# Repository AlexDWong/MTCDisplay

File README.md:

# MTCDisplay

## Description
MTCDisplay is an Arduino-based MIDI Timecode visual display that allows users to view a MIDI Timecode stream on an external LED display. The goal of this project was to create a simple display to enable lighting, audio, and video equipment operators to visually monitor a timecode stream without spending $400+ on a fully-integrated solution.

## Updates
**9/28/2016:** Board version 1.1; see directory for changes.

**8/8/2016:** Board version 1.0 proven.

## Features
* MIDI IN/THRU (DIN-5 connector)
  * 1x MIDI IN
  * Up to 3x MIDI THRU
* 12VDC input with polarity and over-current protection
* Supports all MTC framerates (24, 25, 29.97, 30)
* Mounting holes for custom enclosures and edge clearance for extruded aluminum enclosures

## Physical
* Board Dimensions: 5.00" x 3.35" (127mm x 85.09mm)
* Board Thickness: 1.6mm
* Input Power: +12VDC, 1A (max)
* Input Connections: 2.1mm DC barrel jack, MIDI (DIN-5)
* Output Connections: Up to 3x MIDI (DIN-5)
* Mounting: 4x 0.125" holes at edges of board, 0.1" clearance on sides for insertion into extruded aluminum case

## How it works
MTCDisplay accepts input from a MIDI Timecode stream and displays it on a large, 7-segment display. The displays are driven and controlled by a MAX7219 driver, enabling the Arduino to focus on decoding the MIDI Timecode stream. MTCDisplay supports all four MTC framerates (24/25/29.97 drop-frame/30 frames/s), and the design can be scaled up to support almost any 7-segment, common-cathode LED display.

### "What's (MIDI) Timecode?"

Timecode is a way to synchronize equipment with each other; for instance, an audio track could output a timecode stream to a lighting console so that lighting cues are triggered at exactly the right moment. [MIDI Timecode (MTC)](https://en.wikipedia.org/wiki/MIDI_timecode) is timecode transmitted between devices using the MIDI protocol and interface, and is based off [SMPTE Timecode](https://en.wikipedia.org/wiki/SMPTE_timecode). 

You can read more about the MIDI protocol on [Wikipedia](https://en.wikipedia.org/wiki/MIDI) or on the [official MIDI Association website](https://www.midi.org/). 

### MIDI Timecode

MIDI Timecode follows the SMPTE standard for timecode. Each timecode is represented as four 8-bit unsigned integers:
* Hours (hh)
* Minutes (mm)
* Seconds (ss)
* Frames (ff)

Hours, minutes and seconds are self-explanatory. Frames are sub-divisions of seconds, originally referring to a frame of film as SMPTE timecode was originally developed for film use. There are several different framerates, and as a result MIDI Timecode must also transmit the framerate to ensure all devices are kept in sync.

MIDI Timecode messages can take one of two forms:

#### Quarter-frame Timecode

Quarter-frame Timecode messages are used when the timecode stream is running. Each hour, minute, second or frame byte is broken down into two 4-bit values and attached to a 3-bit identifier. Before each piece is sent, it is preceded by a single status byte (0xF1).

| Piece |  ID #  |  Data  |  Full Byte  | Description         |
|:-----:|:------:|:------:|:-----------:|---------------------|
| 0     | `0000` | `ffff` | `0000 ffff` | Frame number lsbits |
| 1     | `0001` | `000f` | `0001 000f` | Frame number msbit  |
| 2     | `0010` | `ssss` | `0010 ssss` | Seconds lsbits      |
| 3     | `0011` | `00ss` | `0011 00ss` | Seconds msbits      |
| 4     | `0100` | `mmmm` | `0100 mmmm` | Minutes lsbits      |
| 5     | `0101` | `00mm` | `0101 00mm` | Minutes msbits      |
| 6     | `0110` | `hhhh` | `0110 hhhh` | Hour lsbits         |
| 7     | `0111` | `0rrh` | `0111 0rrh` | Hour msbit and rate |

**EX:** Timecode = 01:02:03:04, framerate = 30 frames/s

Quarter-frame Timecode = `F1 04 F1 10 F1 23 F1 30 F1 42 F1 50 F1 61 F1 76`

*Source: [Wikipedia](https://en.wikipedia.org/wiki/MIDI_timecode)*

#### Full Timecode

If the timecode stream suddenly jumps (i.e. jumping ahead in an audio track) a full timecode is sent so that all equipment can resync. Full timecode messages are 10 bytes long, and once transmitted the MTC stream reverts back to quarter-frame messages; full timecode messages are structured as follows:
	`F0 7F 7F 01 01 hh mm ss ff F7`
In it's current state, MTCDisplay only supports quarter-frame messages. If the timecode input jumps, the change will not be reflected on MTCDisplay until the next quarter-frame message is received.

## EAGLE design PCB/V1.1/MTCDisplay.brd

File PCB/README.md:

#PCB Files

Enclosed here are the files needed to have a PCB manufactured, as well as a Bill of Materials.

## Important Note:
The LED displays do not need a current-limiting resistor; instead, the current is set by an external pullup resistor on the MAX7219. If you choose to use a different 7-segment display, then you may need to select a different value for R12 depending on the per-segment forward voltage and foward current. The [MAX7219 datasheet (PDF)](https://datasheets.maximintegrated.com/en/ds/MAX7219-MAX7221.pdf) contains a table with approximate resistance values for a range of voltages and currents; when in doubt, a higher resistance is better.

## Versions
### Version 1.1
Resolved several issues:
* All capacitors have been replaced with 0805 SMD ceramic variants to reduce board space.
* Board reduced in size slightly.
* Rearranged components for easier hand-soldering.
* LCD display package has been corrected; displays now protrude slightly over the edge of the board instead of being inset 1/4" from the edge.
* MIDI OUT/THRU switch removed; no plans to add MTC output at this time.
* Fixed silkscreen part names and text placement.
* Added 0603 LED for power indication.
* Added 0.100", 2x3 ICSP header to program Arduino directly.
* Added diode to RESET signal for ICSP support.
* Added reverse-polarity and over-current protection to input.

### Version 1.0
Initial release. This version has been tested and is proven to work as described. Only Gerber files and a BOM are included.

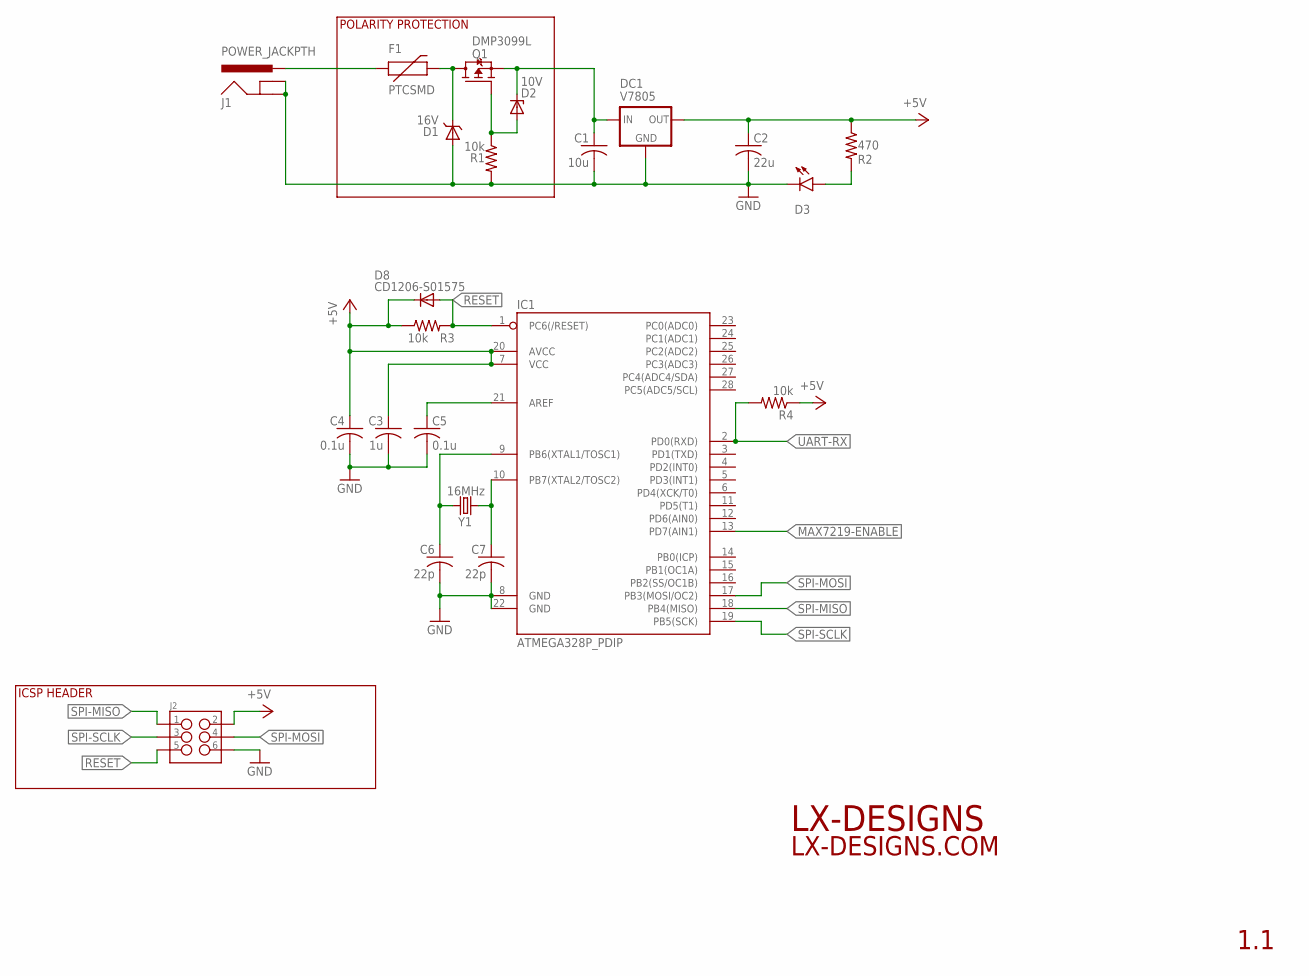
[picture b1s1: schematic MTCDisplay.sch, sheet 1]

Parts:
C1: 10u; C0805K
C2: 22u; C0805K
C3: 1u; C0805K
C4, C5: 0.1u; C0805K
C6, C7: 22p; C0805K
D1: 16V; SOD323-NOSILK
D2: 10V; SOD323
D3: LED0603; LED-0603
D8: CD1206-S01575; MINIMELF
DC1: V7805
F1: PTCSMD; PTC-1206
IC1: ATMEGA328P_PDIP; DIL28-3
J1: POWER_JACKPTH; POWER_JACK_PTH
J2: M03X2NO_SILK; 2X3-NS
Q1: DMP3099L; SOT23
R1, R3, R4: 10k; R0805
R2: 470; R0805
Y1: 16MHz; HC49US

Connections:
5V: C1.1, D2.C, DC1.IN, Q1.2 (S)
+5V: C2.1, C3.1, C4.1, D8.C, DC1.OUT, IC1.7 (VCC), IC1.20 (AVCC), J2.2, R2.1, R3.1, R4.1; also elsewhere on the board
GND: C1.2, C2.2, C3.2, C4.2, C5.2, C6.2, C7.2, D1.A, D3.C, DC1.GND, IC1.8 (GND), IC1.22 (GND), J1.GND, J1.GNDBREAK, J2.6, R1.2; also elsewhere on the board
MAX7219-ENABLE: IC1.13 (PD7(AIN1)); also elsewhere on the board
unnamed: C6.1, IC1.9 (PB6(XTAL1/TOSC1)), Y1.2
unnamed: C5.1, IC1.21 (AREF)
unnamed: D3.A, R2.2
unnamed: C7.1, IC1.10 (PB7(XTAL2/TOSC2)), Y1.1
unnamed: F1.1, J1.PWR
unnamed: D1.C, F1.2, Q1.3 (D)
unnamed: D2.A, Q1.1 (G), R1.1
RESET: D8.A, IC1.1 (PC6(/RESET)), J2.5, R3.2
SPI-MISO: IC1.18 (PB4(MISO)), J2.1
SPI-MOSI: IC1.17 (PB3(MOSI/OC2)), J2.4; also elsewhere on the board
SPI-SCLK: IC1.19 (PB5(SCK)), J2.3; also elsewhere on the board
UART-RX: IC1.2 (PD0(RXD)), R4.2; also elsewhere on the board

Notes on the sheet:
POLARITY PROTECTION
ICSP HEADER
LX-DESIGNS
LX-DESIGNS.COM
1.1

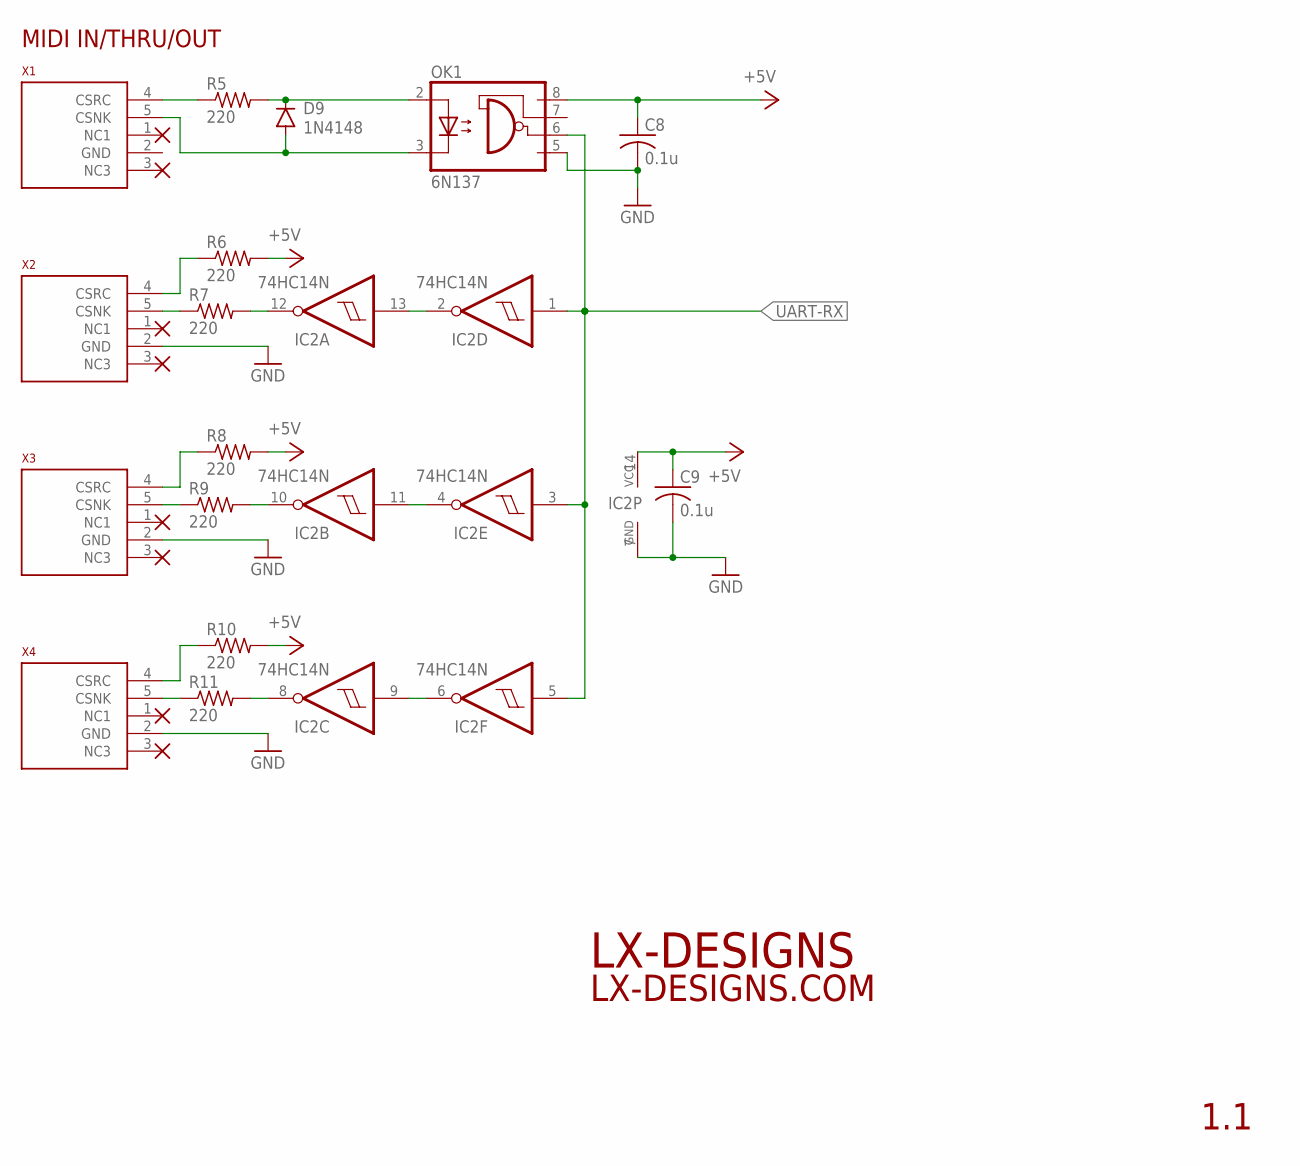
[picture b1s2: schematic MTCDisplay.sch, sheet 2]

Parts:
C8, C9: 0.1u; C0805K
D9: 1N4148; DIODE-1N4148
IC2: 74HC14N; DIL14
OK1: 6N137; DIL08
R5, R6, R7, R8, R9, R10, R11: 220; R0805
X1, X2, X3, X4: 57PC5FSWITCHCRAFT; DIN_5_FEMALE_SUPPORT

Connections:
+5V: C8.1, C9.1, IC2.14 (VCC), OK1.8 (VCC), R6.2, R8.2, R10.2; also elsewhere on the board
GND: C8.2, C9.2, IC2.7 (GND), OK1.5 (GND), X2.2 (GND), X3.2 (GND), X4.2 (GND); also elsewhere on the board
unnamed: R5.1, X1.4 (CSRC)
unnamed: D9.C, OK1.2 (A), R5.2
unnamed: D9.A, OK1.3 (C), X1.5 (CSNK)
unnamed: IC2.2 (O), IC2.13 (I)
unnamed: IC2.12 (O), R7.2
unnamed: IC2.10 (O), R9.2
unnamed: R7.1, X2.5 (CSNK)
unnamed: R6.1, X2.4 (CSRC)
unnamed: IC2.8 (O), R11.2
unnamed: R9.1, X3.5 (CSNK)
unnamed: R8.1, X3.4 (CSRC)
unnamed: IC2.4 (O), IC2.11 (I)
unnamed: IC2.6 (O), IC2.9 (I)
unnamed: R11.1, X4.5 (CSNK)
unnamed: R10.1, X4.4 (CSRC)
UART-RX: IC2.1 (I), IC2.3 (I), IC2.5 (I), OK1.6 (VO); also elsewhere on the board

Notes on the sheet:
MIDI IN/THRU/OUT
LX-DESIGNS
LX-DESIGNS.COM
1.1

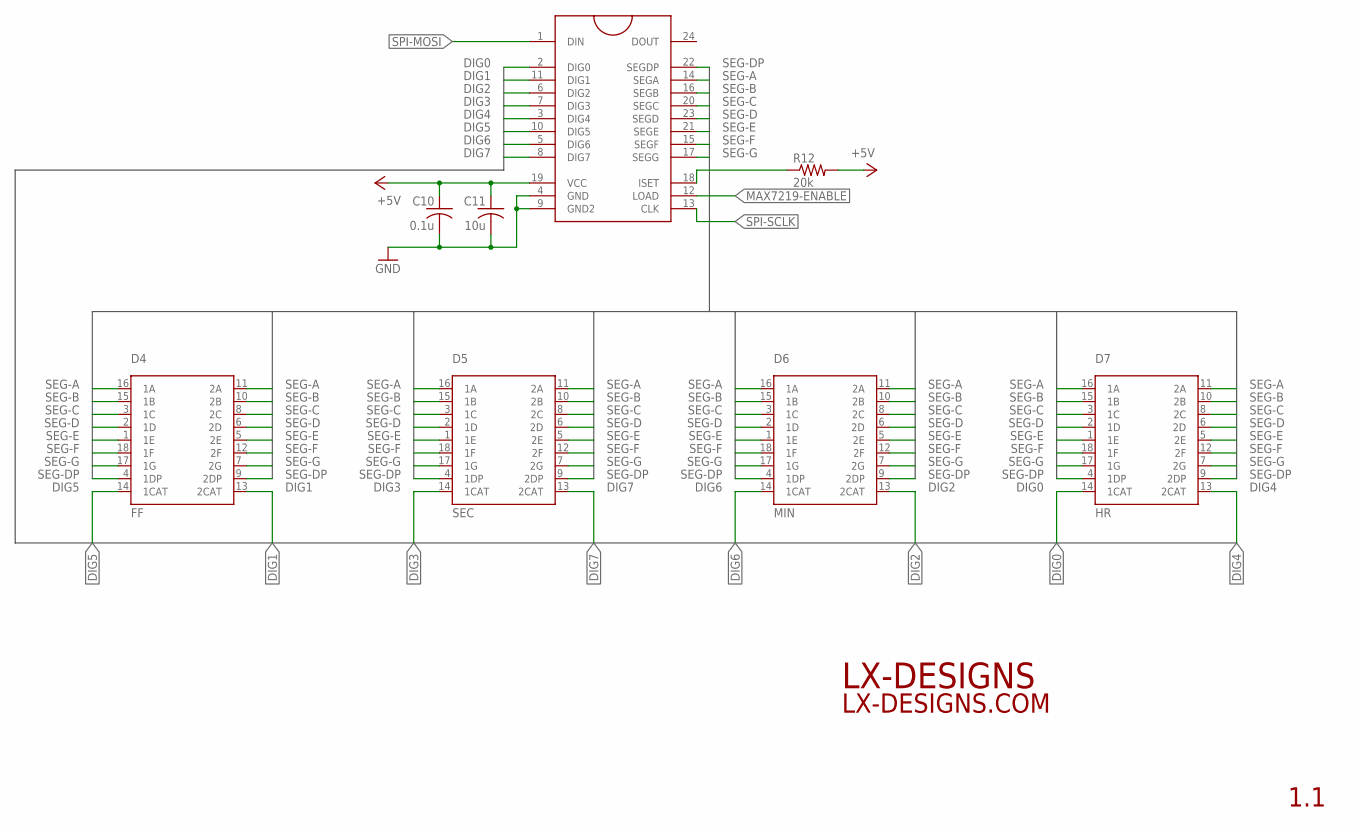
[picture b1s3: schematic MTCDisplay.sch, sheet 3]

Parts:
C10: 0.1u; C0805K
C11: 10u; C0805K
D4: FF; 299-XX-43-618-10-002000
D5: SEC; 299-XX-43-618-10-002000
D6: MIN; 299-XX-43-618-10-002000
D7: HR; 299-XX-43-618-10-002000
IC3: MAX7219DIP; DIL24
R12: 20k; R0805

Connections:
+5V: C10.1, C11.1, IC3.19 (VCC), R12.2; also elsewhere on the board
DIG0: D7.14 (1CAT), IC3.2 (DIG0)
DIG1: D4.13 (2CAT), IC3.11 (DIG1)
DIG2: D6.13 (2CAT), IC3.6 (DIG2)
DIG3: D5.14 (1CAT), IC3.7 (DIG3)
DIG4: D7.13 (2CAT), IC3.3 (DIG4)
DIG5: D4.14 (1CAT), IC3.10 (DIG5)
DIG6: D6.14 (1CAT), IC3.5 (DIG6)
DIG7: D5.13 (2CAT), IC3.8 (DIG7)
GND: C10.2, C11.2, IC3.4 (GND), IC3.9 (GND2); also elsewhere on the board
MAX7219-ENABLE: IC3.12 (LOAD); also elsewhere on the board
unnamed: IC3.18 (ISET), R12.1
SEG-A: D4.11 (2A), D4.16 (1A), D5.11 (2A), D5.16 (1A), D6.11 (2A), D6.16 (1A), D7.11 (2A), D7.16 (1A), IC3.14 (SEGA)
SEG-B: D4.10 (2B), D4.15 (1B), D5.10 (2B), D5.15 (1B), D6.10 (2B), D6.15 (1B), D7.10 (2B), D7.15 (1B), IC3.16 (SEGB)
SEG-C: D4.3 (1C), D4.8 (2C), D5.3 (1C), D5.8 (2C), D6.3 (1C), D6.8 (2C), D7.3 (1C), D7.8 (2C), IC3.20 (SEGC)
SEG-D: D4.2 (1D), D4.6 (2D), D5.2 (1D), D5.6 (2D), D6.2 (1D), D6.6 (2D), D7.2 (1D), D7.6 (2D), IC3.23 (SEGD)
SEG-DP: D4.4 (1DP), D4.9 (2DP), D5.4 (1DP), D5.9 (2DP), D6.4 (1DP), D6.9 (2DP), D7.4 (1DP), D7.9 (2DP), IC3.22 (SEGDP)
SEG-E: D4.1 (1E), D4.5 (2E), D5.1 (1E), D5.5 (2E), D6.1 (1E), D6.5 (2E), D7.1 (1E), D7.5 (2E), IC3.21 (SEGE)
SEG-F: D4.12 (2F), D4.18 (1F), D5.12 (2F), D5.18 (1F), D6.12 (2F), D6.18 (1F), D7.12 (2F), D7.18 (1F), IC3.15 (SEGF)
SEG-G: D4.7 (2G), D4.17 (1G), D5.7 (2G), D5.17 (1G), D6.7 (2G), D6.17 (1G), D7.7 (2G), D7.17 (1G), IC3.17 (SEGG)
SPI-MOSI: IC3.1 (DIN); also elsewhere on the board
SPI-SCLK: IC3.13 (CLK); also elsewhere on the board

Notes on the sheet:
LX-DESIGNS
LX-DESIGNS.COM
1.1

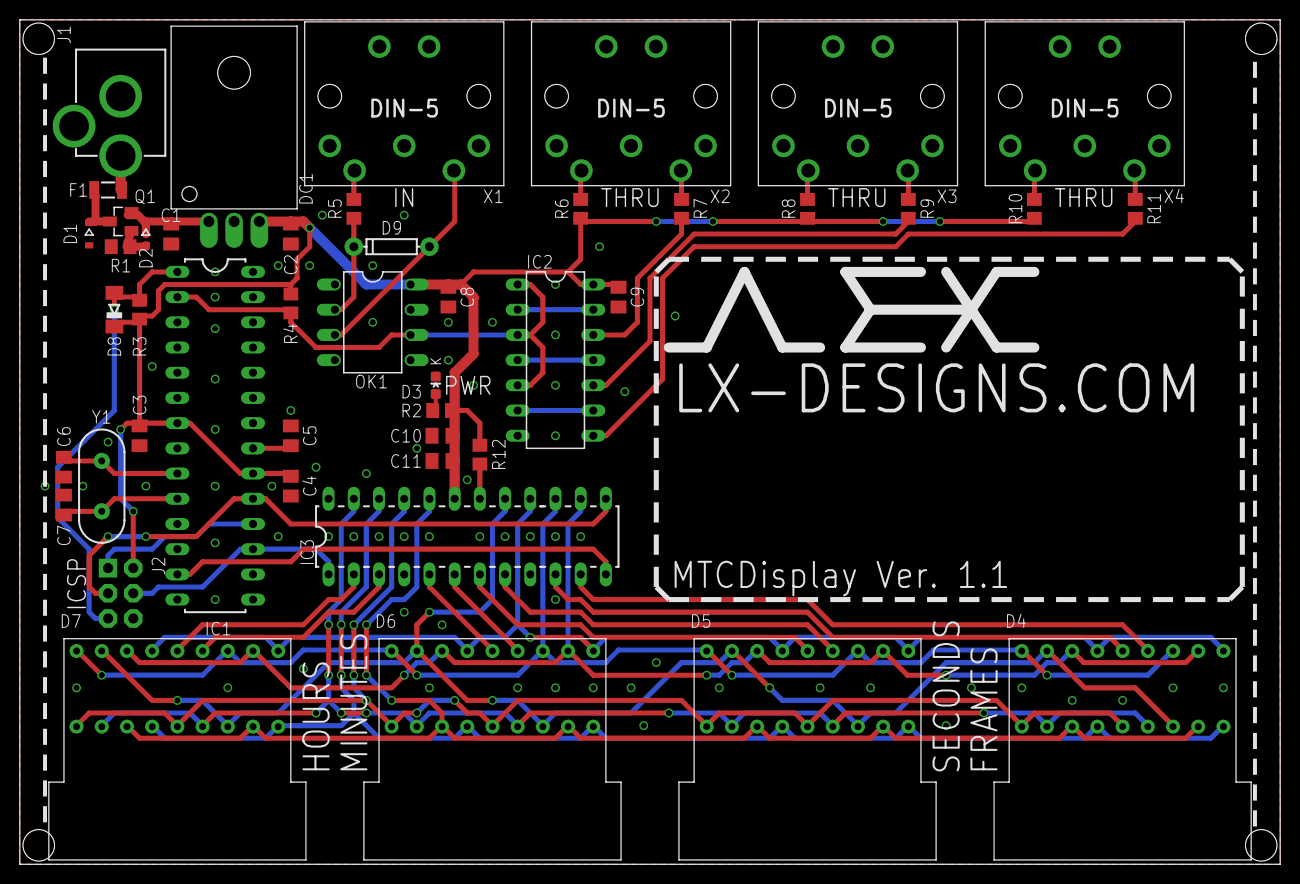
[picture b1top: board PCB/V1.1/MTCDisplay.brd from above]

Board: 2 copper layers, 127.0 x 85.1 mm, 46 parts (0 on the bottom side), 48 nets.

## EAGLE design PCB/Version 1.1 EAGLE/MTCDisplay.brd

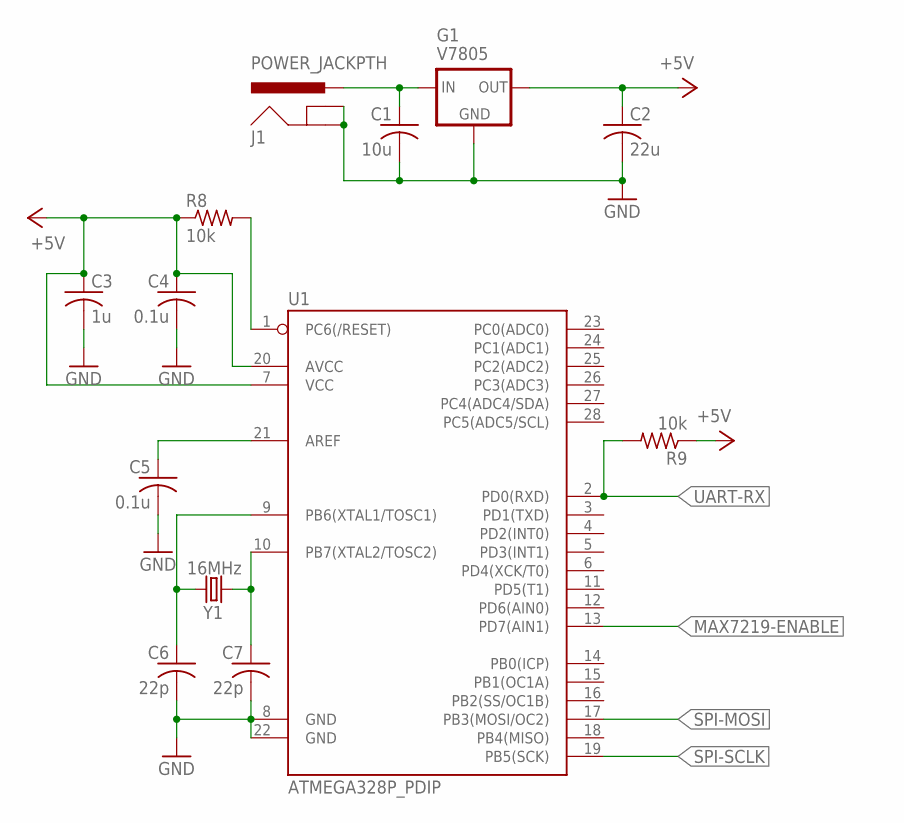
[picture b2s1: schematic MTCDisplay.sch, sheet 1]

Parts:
C1: 10u; C0805K
C2: 22u; C0805K
C3: 1u; C0805K
C4, C5: 0.1u; C0805K
C6, C7: 22p; C0805K
G1: V7805
J1: POWER_JACKPTH; POWER_JACK_PTH
R8, R9: 10k; R2012W
U1: ATMEGA328P_PDIP; DIL28-3
Y1: 16MHz; HC49US

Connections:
+5V: C2.1, C3.1, C4.1, G1.OUT, R8.1, R9.1, U1.7 (VCC), U1.20 (AVCC); also elsewhere on the board
GND: C1.2, C2.2, C3.2, C4.2, C5.2, C6.2, C7.2, G1.GND, J1.GND, J1.GNDBREAK, U1.8 (GND), U1.22 (GND); also elsewhere on the board
MAX7219-ENABLE: U1.13 (PD7(AIN1)); also elsewhere on the board
unnamed: C6.1, U1.9 (PB6(XTAL1/TOSC1)), Y1.2
unnamed: R8.2, U1.1 (PC6(/RESET))
unnamed: C5.1, U1.21 (AREF)
unnamed: C7.1, U1.10 (PB7(XTAL2/TOSC2)), Y1.1
unnamed: C1.1, G1.IN, J1.PWR
SPI-MOSI: U1.17 (PB3(MOSI/OC2)); also elsewhere on the board
SPI-SCLK: U1.19 (PB5(SCK)); also elsewhere on the board
UART-RX: R9.2, U1.2 (PD0(RXD)); also elsewhere on the board

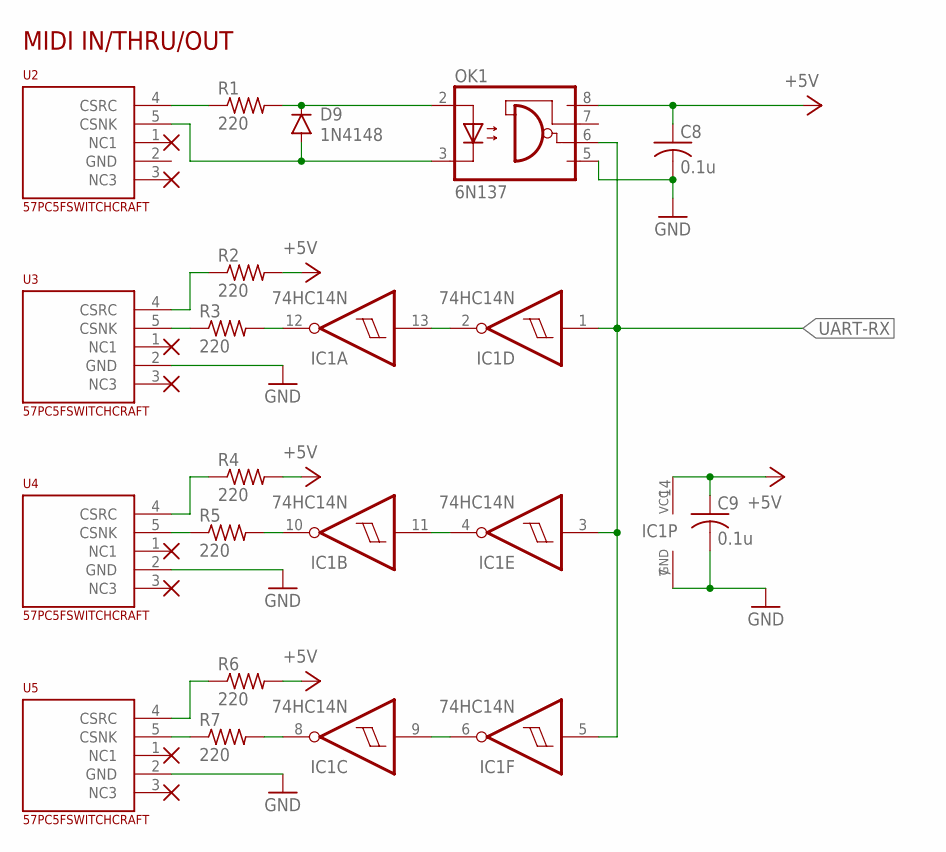
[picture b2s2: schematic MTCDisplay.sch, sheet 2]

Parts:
C8, C9: 0.1u; C0805K
D9: 1N4148; DIODE-1N4148
IC1: 74HC14N; DIL14
OK1: 6N137; DIL08
R1, R2, R3, R4, R5, R6, R7: 220; R2012W
U2, U3, U4, U5: 57PC5FSWITCHCRAFT; DIN_5_FEMALE_SUPPORT

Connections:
+5V: C8.1, C9.1, IC1.14 (VCC), OK1.8 (VCC), R2.2, R4.2, R6.2; also elsewhere on the board
GND: C8.2, C9.2, IC1.7 (GND), OK1.5 (GND), U3.2 (GND), U4.2 (GND), U5.2 (GND); also elsewhere on the board
unnamed: R1.1, U2.4 (CSRC)
unnamed: D9.C, OK1.2 (A), R1.2
unnamed: D9.A, OK1.3 (C), U2.5 (CSNK)
unnamed: IC1.2 (O), IC1.13 (I)
unnamed: IC1.12 (O), R3.2
unnamed: IC1.10 (O), R5.2
unnamed: R3.1, U3.5 (CSNK)
unnamed: R2.1, U3.4 (CSRC)
unnamed: IC1.8 (O), R7.2
unnamed: R5.1, U4.5 (CSNK)
unnamed: R4.1, U4.4 (CSRC)
unnamed: IC1.4 (O), IC1.11 (I)
unnamed: IC1.6 (O), IC1.9 (I)
unnamed: R7.1, U5.5 (CSNK)
unnamed: R6.1, U5.4 (CSRC)
UART-RX: IC1.1 (I), IC1.3 (I), IC1.5 (I), OK1.6 (VO); also elsewhere on the board

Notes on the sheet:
MIDI IN/THRU/OUT

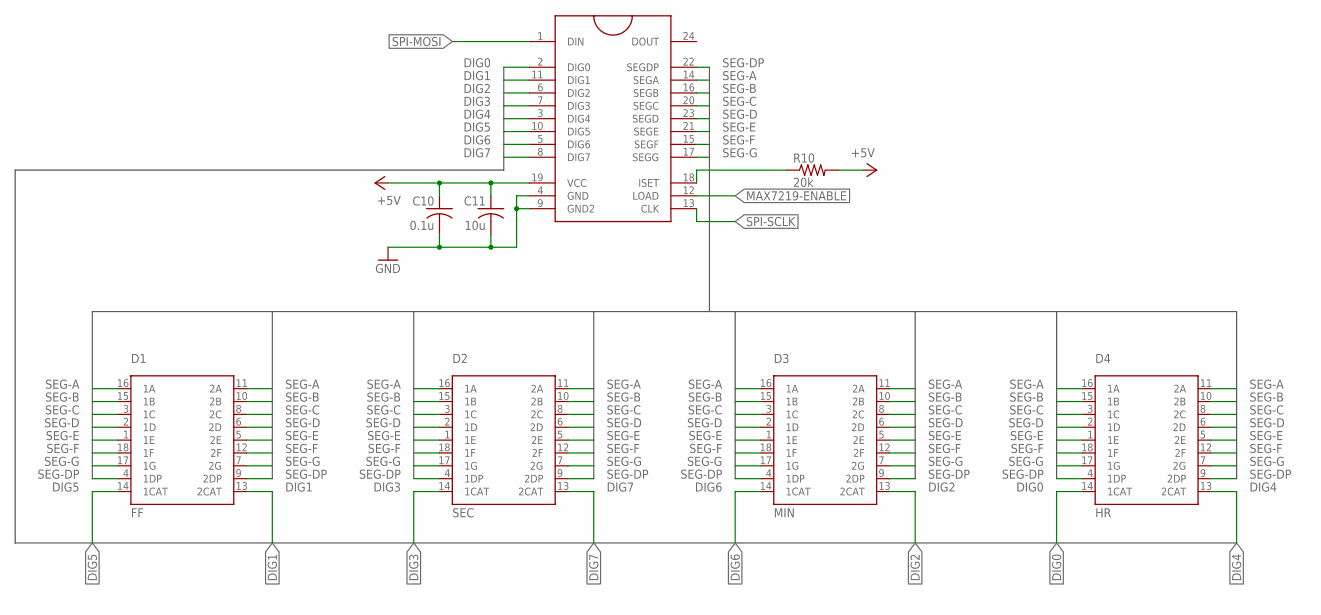
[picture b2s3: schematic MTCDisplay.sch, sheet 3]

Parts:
C10: 0.1u; C0805K
C11: 10u; C0805K
D1: FF; 299-XX-43-618-10-002000
D2: SEC; 299-XX-43-618-10-002000
D3: MIN; 299-XX-43-618-10-002000
D4: HR; 299-XX-43-618-10-002000
R10: 20k; R2012W
U6: MAX7219DIP; DIL24

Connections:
+5V: C10.1, C11.1, R10.2, U6.19 (VCC); also elsewhere on the board
DIG0: D4.14 (1CAT), U6.2 (DIG0)
DIG1: D1.13 (2CAT), U6.11 (DIG1)
DIG2: D3.13 (2CAT), U6.6 (DIG2)
DIG3: D2.14 (1CAT), U6.7 (DIG3)
DIG4: D4.13 (2CAT), U6.3 (DIG4)
DIG5: D1.14 (1CAT), U6.10 (DIG5)
DIG6: D3.14 (1CAT), U6.5 (DIG6)
DIG7: D2.13 (2CAT), U6.8 (DIG7)
GND: C10.2, C11.2, U6.4 (GND), U6.9 (GND2); also elsewhere on the board
MAX7219-ENABLE: U6.12 (LOAD); also elsewhere on the board
unnamed: R10.1, U6.18 (ISET)
SEG-A: D1.11 (2A), D1.16 (1A), D2.11 (2A), D2.16 (1A), D3.11 (2A), D3.16 (1A), D4.11 (2A), D4.16 (1A), U6.14 (SEGA)
SEG-B: D1.10 (2B), D1.15 (1B), D2.10 (2B), D2.15 (1B), D3.10 (2B), D3.15 (1B), D4.10 (2B), D4.15 (1B), U6.16 (SEGB)
SEG-C: D1.3 (1C), D1.8 (2C), D2.3 (1C), D2.8 (2C), D3.3 (1C), D3.8 (2C), D4.3 (1C), D4.8 (2C), U6.20 (SEGC)
SEG-D: D1.2 (1D), D1.6 (2D), D2.2 (1D), D2.6 (2D), D3.2 (1D), D3.6 (2D), D4.2 (1D), D4.6 (2D), U6.23 (SEGD)
SEG-DP: D1.4 (1DP), D1.9 (2DP), D2.4 (1DP), D2.9 (2DP), D3.4 (1DP), D3.9 (2DP), D4.4 (1DP), D4.9 (2DP), U6.22 (SEGDP)
SEG-E: D1.1 (1E), D1.5 (2E), D2.1 (1E), D2.5 (2E), D3.1 (1E), D3.5 (2E), D4.1 (1E), D4.5 (2E), U6.21 (SEGE)
SEG-F: D1.12 (2F), D1.18 (1F), D2.12 (2F), D2.18 (1F), D3.12 (2F), D3.18 (1F), D4.12 (2F), D4.18 (1F), U6.15 (SEGF)
SEG-G: D1.7 (2G), D1.17 (1G), D2.7 (2G), D2.17 (1G), D3.7 (2G), D3.17 (1G), D4.7 (2G), D4.17 (1G), U6.17 (SEGG)
SPI-MOSI: U6.1 (DIN); also elsewhere on the board
SPI-SCLK: U6.13 (CLK); also elsewhere on the board

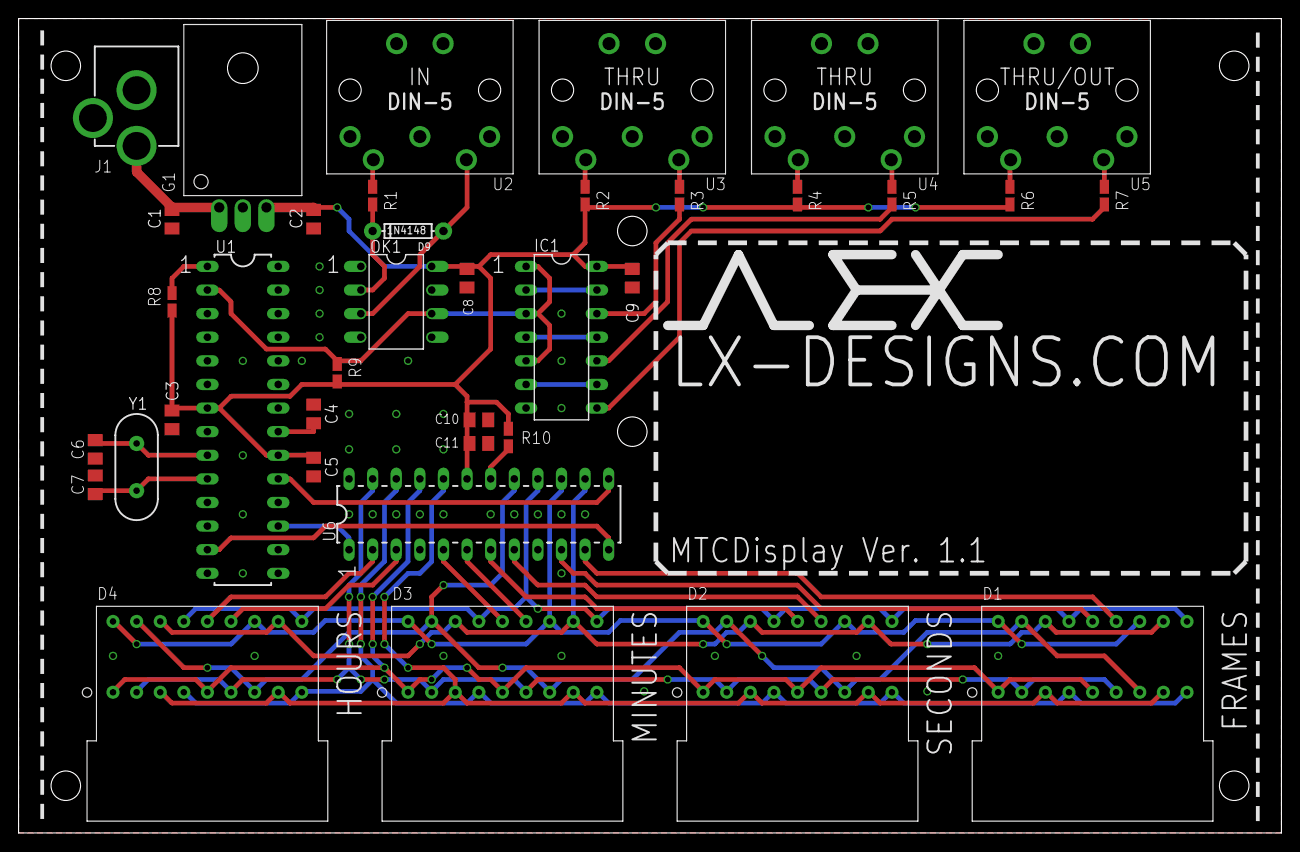
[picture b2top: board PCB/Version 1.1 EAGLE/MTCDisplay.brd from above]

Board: 2 copper layers, 135.9 x 87.6 mm, 37 parts (0 on the bottom side), 43 nets.

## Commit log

2016-07-18 working MTC display
2016-07-18 fix digit flickering
2016-07-29 display decimal point to separate h/m/s/f
2016-08-04 PCB Gerber files rev 1.0
2016-08-09 updated register/digit mapping to match PCB trace layout
2016-08-09 New PCB revision
2016-08-09 include BOM
2016-08-09 update v1.1 schematics (replace 0.1uF cap package, add part names)
2016-08-09 Add info regarding optional parts and changes
2016-08-29 Update segment display package
2016-08-30 Remove MIDI OUT, replace all TH capacitor with SMD
2016-09-28 add gitignore
2016-09-28 Revision 1.1 proven
2016-09-28 Clean directories
2016-09-28 V1.0 BOM
2016-09-28 Remove EAGLE-generated BOM
2016-09-28 Board/Schematic images
2016-09-29 Update License
2016-10-01 Update V1.1 notes, add note about Rset
2016-10-01 Renumber schematic PNGs

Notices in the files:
parts and their libraries:
SparkFun-DiscreteSemi: Licensing: Creative Commons ShareAlike 4.0 International - https://creativecommons.org/licenses/by-sa/4.0
